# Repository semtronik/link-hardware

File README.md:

# link-hardware

Hardware design sources for the **Link** platform: a common ESP32-S3 base
board paired with interchangeable interface modules, in a shared MJF
enclosure.

| Product | Interface | Status |
|---|---|---|
| **Link-LR** | LoRa P2P, 868/915 MHz | first product |
| **Link-485** | RS485 | planned |

> **Current revisions** — base board `0.2.0`, LoRa module `0.2.0`,
> enclosure `0.1.0`. Both boards are validated on the bench; the enclosure
> sources are those of the first print.

This repository holds the design sources. The desktop application lives in
[`link-studio`](https://github.com/semtronik/link-studio), the device firmware
in [`link-firmware`](https://github.com/semtronik/link-firmware), and the
product overview and device↔app protocol in
[`link`](https://github.com/semtronik/link).

## Layout

```
board/
├── link-base-brd/      base board: MCU, display, power
└── link-mod-lr-brd/    LoRa interface module
mechanical/             enclosure
```

Each artifact folder is self-contained — sources, its own `.gitignore`, and
its `outputs/` — so it could be extracted into a standalone repository
without losing anything.

Top-level folders name a **discipline**, not an artifact type: one discipline
can produce several types (`mechanical/` will also hold the front faces).
Folder names are free to change; the tokens in file names are not.

## Setup

Boards reference a shared component library kept in a separate
repository, [`semtronik-kicad-libs`](https://github.com/semtronik/semtronik-kicad-libs).

1. Clone it next to this repository.
2. In KiCad, go to **Preferences → Configure Paths** and add an
   environment variable `SEMTRONIK_KICAD_LIBS` pointing to your local
   clone.

## Reading a file name

Every file is fully qualified, so it can be sent to a fab or a printer on its
own and still say what it is:

```
link-<artifact>[-<variant>]-<type>
```

| Token | Meaning |
|---|---|
| `-brd` | Printed circuit board (KiCad project) |
| `-case` | Enclosure (Fusion 360) |
| `-face` | PET front face (artwork + cutting) |

So `link-mod-lr-brd` is the LoRa interface module board, and
`link-case-top-v0.1.0.step` is the top half of version 0.1.0 of the
enclosure.

## Versions

Hardware follows semantic versioning, with hardware semantics:

- **MAJOR** — breaking: base↔module connector pinout, mounting or dimensions
  changed. A `1.x` module no longer fits a `2.x` base.
- **MINOR** — compatible evolution: component added, protection improved,
  layout reworked. All interfaces stay valid.
- **PATCH** — no functional change: silkscreen fix, component value, routing
  defect.

`0.x` means **pre-production**: the design is under validation and breaking
changes happen without a MAJOR bump. `1.0.0` is the revision customers
physically own — from then on, compatibility is a contract.

Each artifact is versioned independently: the base board can be at `1.0.0`
while a module is still at `0.2.0`.

The version of a physical board is printed on its **silkscreen** — that is
what to quote when reporting an issue. It also appears in the schematic
title block and in the file names under `outputs/`.

## Outputs and releases

Each artifact folder carries an `outputs/` directory holding the fab-agnostic
exports of its **last freeze**: schematic PDF, BOM, position file, gerbers and
STEP.

They are generated from the KiCad jobset committed next to the sources
(`outputs.kicad_jobset`): open the project, run the jobset, and every output
is produced and named in one click. Output names are templated as
`${PROJECTNAME}-v${REVISION}-...`, so the version comes from the schematic
title block and is never typed in — an export cannot carry a version the
source does not state.

`main` only ever contains revisions that were manufactured **and** physically
validated, so what is in `outputs/` on `main` always describes the sources
next to it. Work in progress lives on branches, where that guarantee does not
hold.

Published releases carry the same files, attached to the freeze tag:

```
link-base-brd/v0.2.0
link-mod-lr-brd/v0.2.0
```

Fab-branded exports (vendor plugin folders) are never committed and never
released: releases stay fab-agnostic.

## License

Licensed under the **CERN-OHL-S v2** (strongly reciprocal). You may study,
modify, manufacture and sell hardware based on these sources — provided any
modified design is published under the same licence. See `LICENSE`.

Products made from these sources must keep the source location visible on the
external case where practicable (CERN-OHL-S v2 §4).

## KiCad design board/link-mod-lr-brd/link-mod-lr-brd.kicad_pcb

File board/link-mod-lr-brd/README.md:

# link-mod-lr-brd

LoRa interface module of the **Link** platform. Plugged onto the base board,
it makes a Link-LR: a LoRa P2P radio on 868/915 MHz.

Part of [`link-hardware`](../../README.md). See the repository README for
naming, versioning and release conventions.

## Design

| Function | Part |
|---|---|
| LoRa radio | Seeed Wio-SX1262 module (Semtech SX1262, TCXO, RF switch) |
| Base interface | 2×10 header, 2 mm pitch |

The board is 60 × 50 mm. It carries the radio module and little else:
decoupling, pull-ups and the connector to the base. The antenna leaves
through a u.FL to SMA pigtail to the enclosure.

## Connectors

| Ref | Role |
|---|---|
| J2 | To the base board's J3: power (`+3V3`, `+VSYS`, `+VNR`), I²C and the eight module I/Os `IO_MOD01`–`IO_MOD08`, which carry the radio's SPI and control lines |
| J1, J3 | 1×8 sockets, 2.54 mm — not fitted on the Link-LR |

J2 mates with the base's J3, **the platform contract**: its pinout, the
mounting footprint and the 60 × 50 mm outline are what every interface
module must satisfy.

## Radio wiring

| Module I/O | SX1262 |
|---|---|
| `IO_MOD01` | MISO |
| `IO_MOD02` | SCK |
| `IO_MOD03` | MOSI |
| `IO_MOD04` | RF_SW |
| `IO_MOD05` | NRESET |
| `IO_MOD06` | NSS |
| `IO_MOD07` | DIO1 (interrupt) |
| `IO_MOD08` | BUSY |

The SX1262 drives the module's RF switch itself through DIO2, and powers
its TCXO through DIO3; neither pin leaves the module. The module's `RF_SW`
input must stay high for DIO2 to choose the direction: **R3 (10 k to
+3V3) holds it**, so the firmware leaves that pin alone.

## Status

Pre-production (`0.x`). Revision `0.2.0` is validated on our own bench; all
interfaces may still change without a MAJOR bump.

## Files

Design sources are the KiCad project in this folder. `outputs/` holds the
fab-agnostic exports of the last freeze — schematic PDF, BOM, position file,
gerbers and STEP.

They are regenerated by running `outputs.kicad_jobset` from the KiCad
project window. Output names carry the revision read from the schematic
title block, so they cannot drift from the sources.

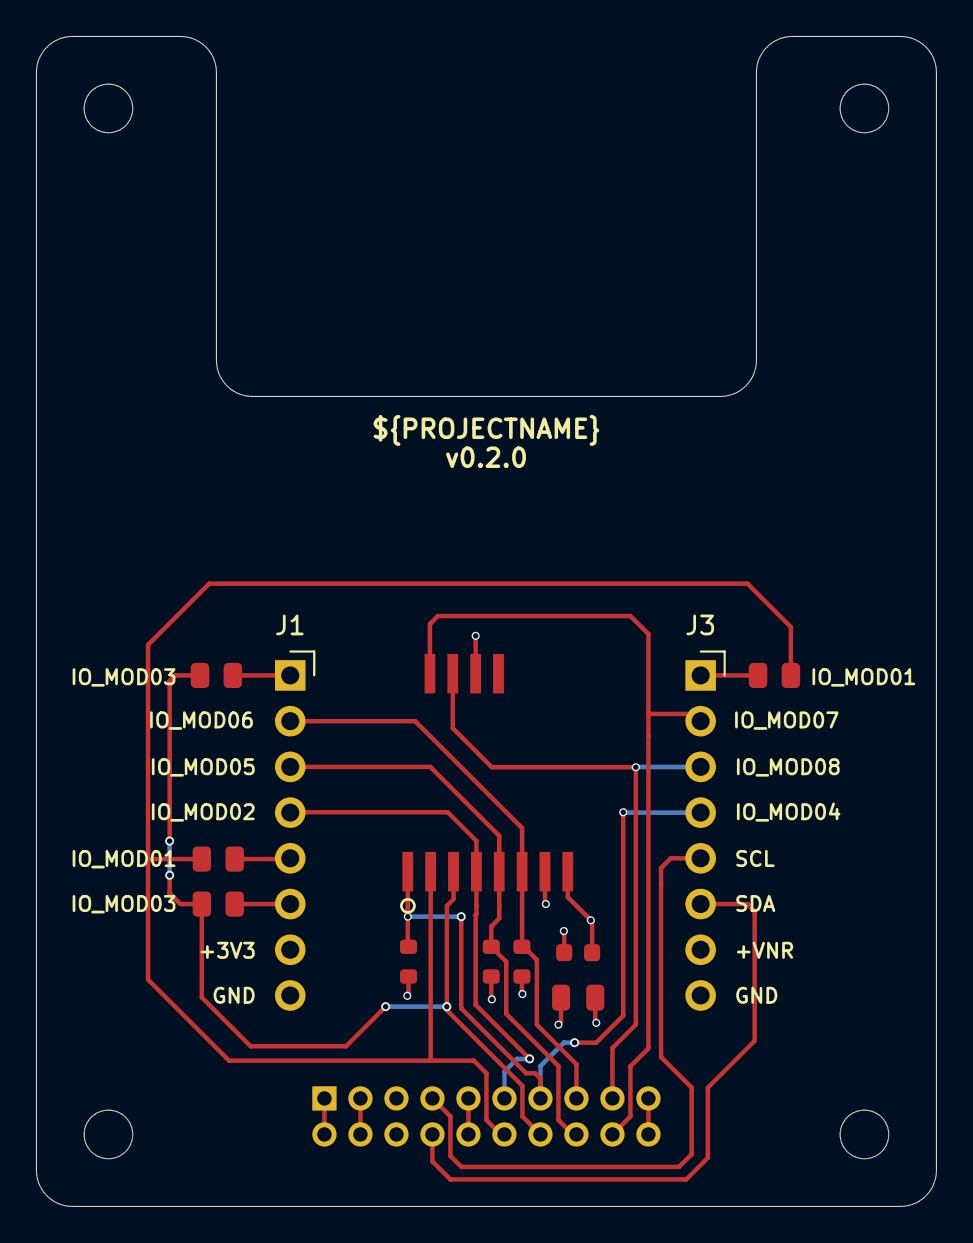
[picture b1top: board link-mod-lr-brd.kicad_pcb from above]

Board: 4 copper layers, 50.0 x 65.0 mm, 18 parts (1 on the bottom side), 18 nets.

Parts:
BRD1: BRD-MIKROE-S
C1: 10uF; C_0805_2012Metric
C2: 0.1uF; C_0603_1608Metric
H1, H2, H3, H4: M2.5; MountingHole_2.7mm_M2.5
J1, J3: Socket-2.54mm-VR; PinSocket_1x08_P2.54mm_Vertical
J2: Header-2x10-2mm-VR; PinHeader_2x10_P2.00mm_Vertical
R1, R2, R3: 10k; R_0603_1608Metric
R4, R5, R6, R7: 0R; R_0805_2012Metric
U1: Wio-SX1262; WioSX1262

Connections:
+3V3: C1.1, C2.1, J1.7, J2.5, J2.6, R2.1, R3.1, U1.8 (VCC)
+VNR: J2.3, J2.4, J3.7
+VSYS: J2.1, J2.2
/WIO-SW1262/AN: J1.1, R4.2
/WIO-SW1262/MISO: J1.5, R6.2
/WIO-SW1262/MOSI: J1.6, R5.2
/WIO-SW1262/PWM: J3.1, R7.2
CORE_SCL: J2.7, J3.5
CORE_SDA: J2.8, J3.6
GND: C1.2, C2.2, J1.8, J2.9, J2.10, J2.19, J2.20, J3.8, R1.2, U1.7 (GND_1), U1.10 (GND_2)
IO_MOD01: J2.12, R6.1, R7.1, U1.2 (MISO)
IO_MOD02: J1.4, J2.11, U1.4 (SCK)
IO_MOD03: J2.14, R4.1, R5.1, U1.3 (MOSI)
IO_MOD04: J2.13, J3.4, R3.2, U1.1 (RF_SW)
IO_MOD05: J1.3, J2.16, R1.1, U1.5 (NRST)
IO_MOD06: J1.2, J2.15, R2.2, U1.6 (NSS)
IO_MOD07: J2.18, J3.2, U1.12 (DIO1)
IO_MOD08: J2.17, J3.3, U1.11 (BUSY)

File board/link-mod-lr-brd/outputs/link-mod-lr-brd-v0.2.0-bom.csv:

"Reference","Quantity","Description","Manufacturer","Manufacturer PN","DNP","Notes"
"C1","1","Capacitor, 10uF, 25V, X5R, 0805","Samsung","CL21A106KAYNNNE","",""
"C2","1","Capacitor, 0.1uF, 50V, X7R, 0603","Yageo","CC0603KRX7R9BB104","",""
"J1,J3","2","Connector, Header, 1x8, 2.54mm, Vertical , TH","Wurth","61300811821","DNP",""
"J2","1","Connector, Header, 2x10, 2mm, Vertical, TH","GCT","BF050-20-A-B-0400-0300-L-G","",""
"R1,R2,R3","3","Resistor,10k, 1%, 0.1W, 0603","Yageo","RC0603FR-0710KL","",""
"R4,R5,R6,R7","4","Resistor, 0R, 0805","Yageo","RC0805FR-070RL","DNP",""
"U1","1","IC, RF, Lora, SMD","SeedStudio","wio-sx1262","",""

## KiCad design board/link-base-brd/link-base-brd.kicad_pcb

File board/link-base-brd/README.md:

# link-base-brd

Base board of the **Link** platform: MCU, display, power and battery
management. It carries no field interface of its own — that is the job of the
interface module it hosts, which makes the same base a Link-LR or a Link-485.

Part of [`link-hardware`](../../README.md). See the repository README for
naming, versioning and release conventions.

## Design

| Function | Part |
|---|---|
| MCU | ESP32-S3-WROOM-1-N16R8 (16 MB flash, 8 MB PSRAM) |
| Battery charger | BQ24074RGT — USB or Li-ion input, power path |
| Fuel gauge | MAX17048G+ |
| Buck converter | TPS62821 |
| Real-time clock | PCF8563T + 32.768 kHz crystal |
| Backlight driver | CAT4104V-GT3 |

Power comes from USB-C or a Li-ion cell, with charging and power-path
management on board — the device keeps running while charging.

## Connectors

| Ref | Role |
|---|---|
| J3 | Base↔module interface (2×10, 2 mm) |
| J5 | USB-C (USB 2.0) |
| J6, J7 | Display FPC |
| J1 | Battery (JST-XH) |

**J3 is the platform contract.** Its pinout, the mounting footprint and the
module outline are what every interface module must satisfy. Breaking any of
them is a MAJOR version bump, and means supporting two incompatible fleets.

## Status

Pre-production (`0.x`). The design is under validation on our own bench; all
interfaces may still change without a MAJOR bump.

## Files

Design sources are the KiCad project in this folder. `outputs/` holds the
fab-agnostic exports of the last freeze — schematic PDF, BOM, position file,
gerbers and STEP.

They are regenerated by running `outputs.kicad_jobset` from the KiCad
project window. Output names carry the revision read from the schematic title
block, so they cannot drift from the sources.

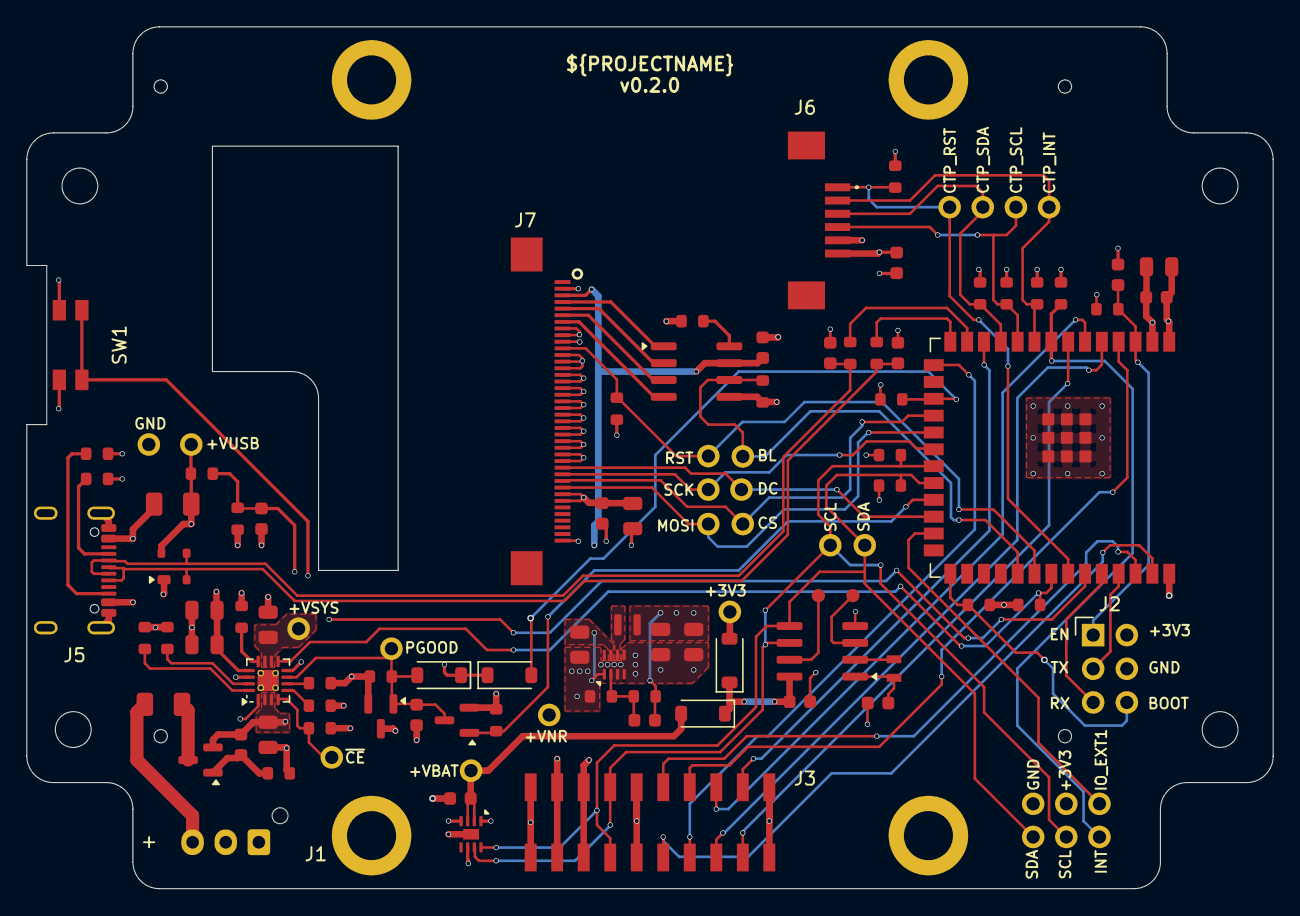
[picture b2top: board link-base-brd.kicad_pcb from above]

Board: 4 copper layers, 94.0 x 65.0 mm, 115 parts (0 on the bottom side), 67 nets.

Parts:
C1, C2, C4, C9, C12, C21, C23: 10uF; C_0805_2012Metric
C3: 10uF; C_0603_1608Metric
C5: 10nF; C_0603_1608Metric
C6, C8, C13, C22, C24, C25: 0.1uF; C_0603_1608Metric
C7: 120pF; C_0603_1608Metric
C10, C11: 22uF; C_0805_2012Metric
C14, C17: 1uF; C_0603_1608Metric
C15, C16, C18: 15pF; C_0603_1608Metric
D1, D2, D3, D4: 1N4148W; D_SOD-123
D6: PRTR5V0U2X; SOT-143
F1, F2: 0.75A; Fuse_1206_3216Metric
H1, H2, H7, H8: Standoff_M2.5x7; WA-SMSI_9774070151
H3, H4, H5, H6: M2.5; MountingHole_2.7mm_M2.5
J1: JST-XH-3P; JST_XH_B3B-XH-AM_1x03_P2.50mm_Vertical
J2: CON-Header-2x03-2.54mm-VR; PinHeader_2x03_P2.54mm_Vertical
J3: CON-Header-2x10-2mm-HR; PinSocket_2x10_P2.00mm_Vertical_SMD
J5: USB_C_Receptacle_USB2.0_16P; USB_C_Receptacle_GCT_USB4105-xx-A_16P_TopMnt_Horizontal
J6: 52271-0679; 522710679
J7: 54132-4062; 54132-4062_1
L1: 470nH 4.5A; L_Murata_DFE201610P
Q1, Q3: AO3401A; SOT-23
Q2: AO3400A; SOT-23
R1, R15, R16, R17, R18, R19, R20, R23, R24, R25: 10k; R_0603_1608Metric
R2: 3k; R_0603_1608Metric
R3, R4, R5, R6, R7, R11, R14, R32, R33, R34: 100k; R_0603_1608Metric
R8: 1.5k; R_0603_1608Metric
R9: 1.8k; R_0603_1608Metric
R10: 1M; R_0603_1608Metric
R12: 453k; R_0603_1608Metric
R13: 150k; R_0603_1608Metric
R21, R22: 22R; R_0603_1608Metric
R30, R31: 5.1k; R_0603_1608Metric
R35: 3.3k; R_0603_1608Metric
SW1: SW-SPST-EVQPUA02K; Panasonic_EVQPUJ_EVQPUA
TP1, TP2, TP3, TP4, TP5, TP6, TP7, TP8, TP9, TP10, TP13, TP14, TP15, TP16, TP17, TP18, TP19, TP20, TP21, TP22, TP23, TP24, TP25, TP26, TP27, TP28: TP-PAD-D1.0mm; TestPoint_THTPad_D1.0mm_Drill0.5mm
TP11, TP12: TP-PAD-D1.0mm; TestPoint_Pad_D1.0mm
U1: BQ24074RGT; VQFN-16-1EP_3x3mm_P0.5mm_EP1.6x1.6mm_ThermalVias
U2: MAX17048G+; TDFN-8-1EP_2x2mm_P0.5mm_EP0.8x1.2mm
U3: TPS62821; Texas_VSON-HR-8_1.5x2mm_P0.5mm
U4: ESP32-S3-WROOM-1-N16R8; ESP32-S3-WROOM-1
U5: PCF8563T; SOIC-8_3.9x4.9mm_P1.27mm
U6: CAT4104V-GT3; SOIC-8_3.9x4.9mm_P1.27mm
Y1: 32.768kHz; Crystal_SMD_2012-2Pin_2.0x1.2mm

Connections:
+3V3: C7.1, C10.1, C11.1, C12.1, C13.1, C22.1, C23.1, C24.1, D3.2 (A), J2.2, J3.5, J3.6, J6.6, J7.8, J7.9, J7.33, J7.34, L1.2, R1.1, R12.1, R15.2, R16.2, R17.2, R18.2, R19.2, R20.2, R23.2, R24.2, R25.1, TP6.1 (1_1), TP18.1 (1_1), U4.2 (3V3)
+VBAT: C4.1, C5.1, C6.1, D4.2 (A), Q3.2 (S), TP5.1 (1_1), U1.2 (BAT), U1.3 (BAT), U2.2 (CELL), U2.3 (VDD)
+VNR: C9.1, C25.1, J3.3, J3.4, J7.3, Q1.3 (D), TP2.1 (1_1), U3.1 (EN), U3.7 (VIN), U6.7 (VIN)
+VSYS: C2.1, J3.1, J3.2, Q1.2 (S), R3.1, R6.1, TP1.1 (1_1), U1.10 (OUT), U1.11 (OUT)
+VUSB: C1.1, C21.1, D6.4 (VCC), F2.2, R11.1, TP13.1 (1_1), U1.13 (IN)
/CORE/BOOT: J2.6, R20.1, U4.27 (GPIO0/BOOT)
/CORE/EN: C14.1, J2.1, R15.1, U4.3 (EN)
/CORE/RXD0: J2.5, U4.36 (U0RXD/GPIO44/CLK_OUT2)
/CORE/TXD0: J2.3, U4.37 (U0TXD/GPIO43/CLK_OUT1)
/IHM/LED-K1: J7.7, U6.4 (LED4)
/IHM/LED-K2: J7.6, U6.3 (LED3)
/IHM/LED-K3: J7.5, U6.2 (LED2)
/IHM/LED-K4: J7.4, U6.1 (LED1)
/PWR/PGOOD: C3.1, D2.2 (A), Q1.1 (G), Q2.3 (D), R3.2, TP4.1 (1_1), U1.7 (~PGOOD)
CHG: R25.2, U1.9 (~CHG), U4.33 (MTDO/GPIO40/CLK_OUT2)
CORE_INT: R23.1, TP20.1 (1_1), U4.8 (GPIO15/U0RTS/ADC2_CH4/XTAL_32K_P)
CORE_SCL: J3.8, R16.1, TP7.1 (1_1), TP21.1 (1_1), U2.7 (SCL), U4.21 (GPIO13/TOUCH13/ADC2_CH2), U5.6 (SCL)
CORE_SDA: J3.7, R17.1, TP8.1 (1_1), TP19.1 (1_1), U2.8 (SDA), U4.22 (GPIO14/TOUCH14/ADC2_CH3), U5.5 (SDA)
CTP_INT: J6.2, R24.1, TP14.1 (1_1), U4.9 (GPIO16/U0CTS/ADC2_CH5/XTAL_32K_N)
CTP_RESET: J6.1, R32.1, TP15.1 (1_1), U4.34 (MTDI/GPIO41/CLK_OUT1)
CTP_SCL: J6.4, R18.1, TP9.1 (1_1), U4.10 (GPIO17/U1TXD/ADC2_CH6)
CTP_SDA: J6.3, R19.1, TP10.1 (1_1), U4.11 (GPIO18/U1RXD/ADC2_CH7/CLK_OUT3)
GND: C1.2, C2.2, C3.2, C4.2, C6.2, C8.2, C9.2, C10.2, C11.2, C12.2, C13.2, C14.2, C15.1, C16.1, C17.2, C18.1, C21.2, C22.2, C23.2, C24.2, C25.2, D6.1 (GND), J1.1, J2.4, J3.9, J3.10, J3.19, J3.20, J5.A1 (GND), J5.A12 (GND), J5.B1 (GND), J5.B12 (GND), J5.S1 (SHIELD), J6.5, J7.2, J7.10, J7.12, J7.13, J7.14, J7.15, J7.16, J7.17, J7.18, J7.19, J7.20, J7.21, J7.22, J7.23, J7.24, J7.25, J7.26, J7.27, J7.28, J7.40, Q2.2 (S), R2.1, R4.1, R5.2, R7.1, R8.1, R9.1, R10.2, R13.2, R14.2, R30.2, R31.2, R32.2, R33.2, R34.2, R35.2, SW1.2, TP16.1 (1_1), TP17.1 (1_1), U1.8 (VSS), U1.14 (TMR), U1.17 (VSS), U2.1 (CTG), U2.4 (GND), U2.6 (QSTRT), U2.9 (EP), U3.3 (AGND), U3.5 (PGND), U4.1 (GND), U4.40 (GND), U4.41 (GND), U5.4 (VSS), U6.5 (GND)
IO_EXT1: TP22.1 (1_1), U4.25 (GPIO48)
IO_MOD1: J3.11, U4.39 (GPIO1/TOUCH1/ADC1_CH0)
IO_MOD2: J3.12, U4.38 (GPIO2/TOUCH2/ADC1_CH1)
IO_MOD3: J3.13, U4.15 (GPIO3/TOUCH3/ADC1_CH2)
IO_MOD4: J3.14, U4.4 (GPIO4/TOUCH4/ADC1_CH3)
IO_MOD5: J3.15, U4.5 (GPIO5/TOUCH5/ADC1_CH4)
IO_MOD6: J3.16, U4.6 (GPIO6/TOUCH6/ADC1_CH5)
IO_MOD7: J3.17, U4.7 (GPIO7/TOUCH7/ADC1_CH6)
IO_MOD8: J3.18, U4.12 (GPIO8/TOUCH8/ADC1_CH7)
LCD_BL: R34.1, TP28.1 (1_1), U4.31 (GPIO38), U6.6 (EN/PWM)
LCD_CS: J7.31, TP25.1 (1_1), U4.18 (GPIO10/TOUCH10/ADC1_CH9)
LCD_DC: J7.29, TP23.1 (1_1), U4.24 (GPIO47)
LCD_MOSI: J7.32, TP26.1 (1_1), U4.19 (GPIO11/TOUCH11/ADC2_CH0)
LCD_RST: J7.11, R33.1, TP27.1 (1_1), U4.32 (MTCK/GPIO39/CLK_OUT3/SUBSPICS1)
LCD_SCK: J7.30, TP24.1 (1_1), U4.20 (GPIO12/TOUCH12/ADC2_CH1)
unnamed: D1.1 (K), D2.1 (K), SW1.1
unnamed: C17.1, D3.1 (K), D4.1 (K), U5.8 (VDD)
unnamed: F2.1, J5.A4 (VBUS), J5.A9 (VBUS), J5.B4 (VBUS), J5.B9 (VBUS)
unnamed: J1.2, U1.1 (TS)
unnamed: F1.2, J1.3
unnamed: J5.A5 (CC1), R31.1
unnamed: J5.B5 (CC2), R30.1
unnamed: F1.1, Q3.3 (D)
unnamed: C5.2, Q3.1 (G), R10.1
unnamed: R6.2, U1.6 (EN1)
unnamed: R7.2, U1.5 (EN2)
unnamed: R8.2, U1.12 (ILIM)
unnamed: R9.2, U1.16 (ISET)
unnamed: R2.2, U1.15 (ITERM)
unnamed: R4.2, TP3.1 (1_1), U1.4 (~CE)
unnamed: C7.2, R12.2, R14.1, U3.2 (FB)
unnamed: L1.1, U3.6 (SW)
unnamed: R21.2, U4.13 (GPIO19/USB_D-)
unnamed: R22.2, U4.14 (GPIO20/USB_D+)
unnamed: TP11.1 (1_1), U5.7 (CLKO)
unnamed: C18.2, U5.1 (OSCI), Y1.2
unnamed: U5.2 (OSCO), Y1.1
unnamed: TP12.1 (1_1), U5.3 (~INT)
unnamed: R35.1, U6.8 (RSET)
PRES_USB: C8.1, R11.2, R13.1, U4.35 (MTMS/GPIO42)
PWR_HOLD: Q2.1 (G), R5.1, U4.23 (GPIO21)
PWR_KEY: D1.2 (A), R1.2, U4.17 (GPIO9/TOUCH9/ADC1_CH8)
USB_D+: C15.2, D6.2 (I/O1), J5.A6 (D+), J5.B6 (D+), R22.1
USB_D-: C16.2, D6.3 (I/O2), J5.A7 (D-), J5.B7 (D-), R21.1

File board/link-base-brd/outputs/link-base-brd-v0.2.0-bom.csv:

"Reference","Quantity","Description","Manufacturer","Manufacturer PN","DNP","Notes"
"C1,C2,C4,C9,C12,C21,C23","7","Capacitor, 10uF, 25V, X5R, 0805","Samsung","CL21A106KAYNNNE","",""
"C3","1","Capacitor, 10uF, 10V, X5R, 0603","TDK","C1608X5R1A106K080AC","",""
"C5","1","Capacitor, 0.01uF, 50V, X7R, 0603","Yageo","CC0603KRX7R9BB103","",""
"C6,C8,C13,C22,C24,C25","6","Capacitor, 0.1uF, 50V, X7R, 0603","Yageo","CC0603KRX7R9BB104","",""
"C7","1","Capacitor, 120pF, 50V, C0G, 0603","Samsung","CL10C121JB81PNC","",""
"C10,C11","2","Capacitor, 22uF, 10V, X5R, 0805","Samsung","CL21A226MPQNNNE","",""
"C14,C17","2","Capacitor, 1uF, 50V, X5R, 0603","Samsung","CL10A105KB8NNNC","",""
"C15,C16,C18","3","Capacitor, 15pF, 50V, C0G, 0603","Samsung","CL10C150JB8NNNC","DNP",""
"D1,D2,D3,D4","4","Diode standard, 75V 250MA, SOD123","SMC Diode Solutions","1N4148W","",""
"D6","1","Diode, TVS, SOT-143","Nexperia","PRTR5V0U2X,215","",""
"F1,F2","2","PTC, 0.75A hold, 6V, 1206","Bourns","MF-NSMF075-2","",""
"J1","1","Connector, Header, 1x3, 2.5mm, TH","JST","B3B-XH-AM","",""
"J2","1","Generic connector, double row, 02x03, odd/even pin numbering scheme (row 1 odd numbers, row 2 even numbers), script generated (kicad-library-utils/schlib/autogen/connector/)","","","DNP",""
"J3","1","Connector, Socket, 2x10, 2mm, Vertical, Height=4.6mm, SMD","Wurth","621320242921","","HCTL - PM200-2-10-S-4.3"
"J5","1","Connector, USB-C Receptacle 16P, USB 2.0, SMD","GCT","USB4105-GF-A","",""
"J6","1","Connector, FPC, 6pos, 1mm, SMD","Molex","52271-0679","",""
"J7","1","Connector, FPC, 40pos, 0.5mm, SMD","Molex","54132-4062","",""
"L1","1","Inductor, 470nH, 4.5A, 26mOhm, 0806","Murata","DFE201612E-R47M=P2","",""
"Q1,Q3","2","Transistor, Mosfet, P-Channel, 4A, 30V, SOT-23","Alpha & Omega Semiconductor Inc.","AO3401A","",""
"Q2","1","Transistor, Mosfet,  N-Channel, 5.7A, 30V, SOT-23","Alpha & Omega Semiconductor Inc.","AO3400A","",""
"R1,R15,R16,R17,R18,R19,R20,R23,R24,R25","10","Resistor,10k, 1%, 0.1W, 0603","Yageo","RC0603FR-0710KL","",""
"R2","1","Resistor,3.k, 1%, 0.1W, 0603","Yageo","RC0603FR-073KL","",""
"R3,R4,R5,R6,R7,R11,R14,R32,R33,R34","10","Resistor,100k, 1%, 0.1W, 0603","Yageo","RC0603FR-07100KL","",""
"R8","1","Resistor,1.5k, 1%, 0.1W, 0603","Yageo","RC0603FR-071K5L","",""
"R9","1","Resistor,1.8k, 1%, 0.1W, 0603","Yageo","RC0603FR-071K8L","",""
"R10","1","Resistor, 1M, 1%, 0.1W, 0603","Yageo","RC0603FR-071ML","",""
"R12","1","Resistor,453k, 1%, 0.1W, 0603","Yageo","RC0603FR-07453KL","",""
"R13","1","Resistor,150k, 1%, 0.1W, 0603","Yageo","RC0603FR-07150KL","",""
"R21,R22","2","Resistor, 22R, 1%, 0.1W, 0603","Yageo","RC0603FR-0722RL","",""
"R30,R31","2","Resistor,5.1k, 1%, 0.1W, 0603","Yageo","RC0603FR-075K1L","",""
"R35","1","Resistor,3.3k, 1%, 0.1W, 0603","Yageo","RC0603FR-073K3L","",""
"SW1","1","Tactile switch, SPST-NO, 0.05A 12V, SMD","Panasonic","EVQ-PUA02K","",""
"U1","1","IC, Li-Ion Battery Charger and Power-Path Management, VQFN-16","Texas Instruments","BQ24074RGTR","",""
"U2","1","IC, BATT MON, LI-ION 1CELL, 8TDFN","Analog Devices","MAX17048G+","",""
"U3","1","IC, Regulator, Buck, ADJ, 1A, QFN-8","Texas Instruments","TPS62821DLCR","",""
"U4","1","IC, MCU, ESP32-S3-WROOM, 16MB Flash, 8MB PSRAM, Int. Ant.","Espressif","ESP32-S3-WROOM-1-N16R8","",""
"U5","1","Realtime Clock/Calendar I2C Interface, SOIC-8","NXP","PCF8563T/5,518","",""
"U6","1","IC, Led Driver Linear, 175mA, 8SOIC","onsemi","CAT4104V-GT3","",""
"Y1","1","Crystal, 32.768Khz, 9pF, SMD","Micro Crystal AG","CM8V-T1A-32.768KHZ-9PF-20PPM-TA-QC","",""
